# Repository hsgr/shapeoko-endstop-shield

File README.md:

# Shapeoko 2 Endstops shield

Simple shield for usage on gShield of Shapeoko 2. See Shapeoko [Limit Switches](http://www.shapeoko.com/wiki/index.php/Home/Limit_Switches) page for more details on wiring and grbl settings.

## License

Licensed under the [CERN OHLv1.2](LICENSE).

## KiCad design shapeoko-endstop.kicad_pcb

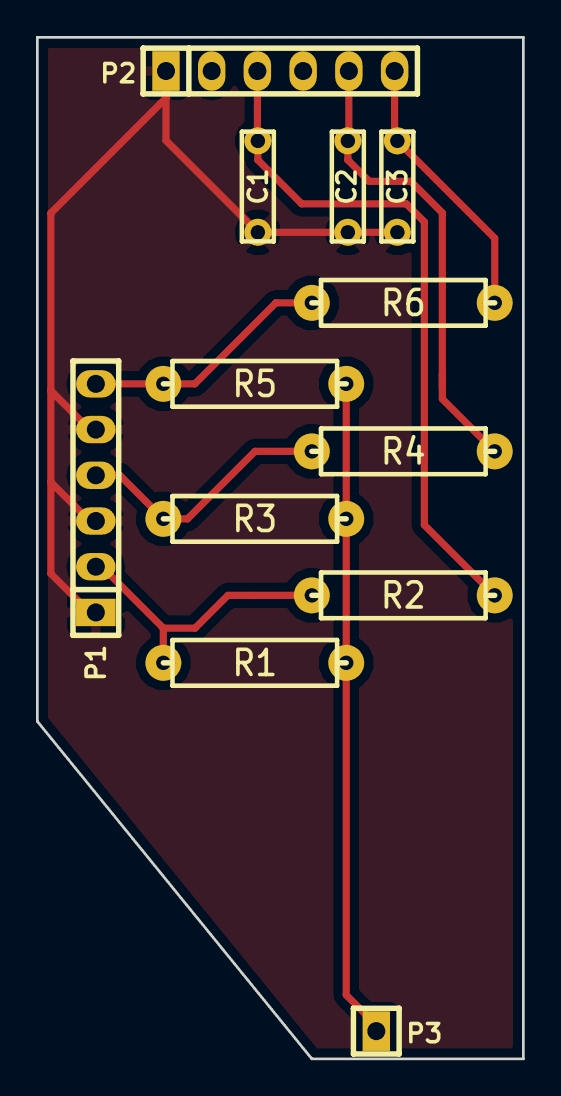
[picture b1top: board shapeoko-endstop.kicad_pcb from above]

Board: 2 copper layers, 27.0 x 56.8 mm, 12 parts (0 on the bottom side), 8 nets.

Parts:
C1, C2, C3: 100n; cnp_6mm_disc
P1, P2: CONN_01X06; pin_strip_6
P3: CONN_01X01; pin_strip_1
R1, R3, R5: 680; RC05
R2, R4, R6: 10k; RC05

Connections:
5V: P3.1, R1.2, R3.2, R5.2
GND: C1.2, C2.2, C3.2, P1.1, P1.3, P1.5, P2.1
X_ARD: C3.1, P2.6, R6.1
X_NO: P1.6, R5.1, R6.2
Y_ARD: C2.1, P2.5, R4.1
Y_NO: P1.4, R3.1, R4.2
Z_ARD: C1.1, P2.3, R2.1
Z_NO: P1.2, R1.1, R2.2

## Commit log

2016-03-10 Initial commit.
2019-11-15 Add end stop bracket
